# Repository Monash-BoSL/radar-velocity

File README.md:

# radar-velocity
Here we dedicate this repository to the development of a device to measure water surface velocity using mm wave radar

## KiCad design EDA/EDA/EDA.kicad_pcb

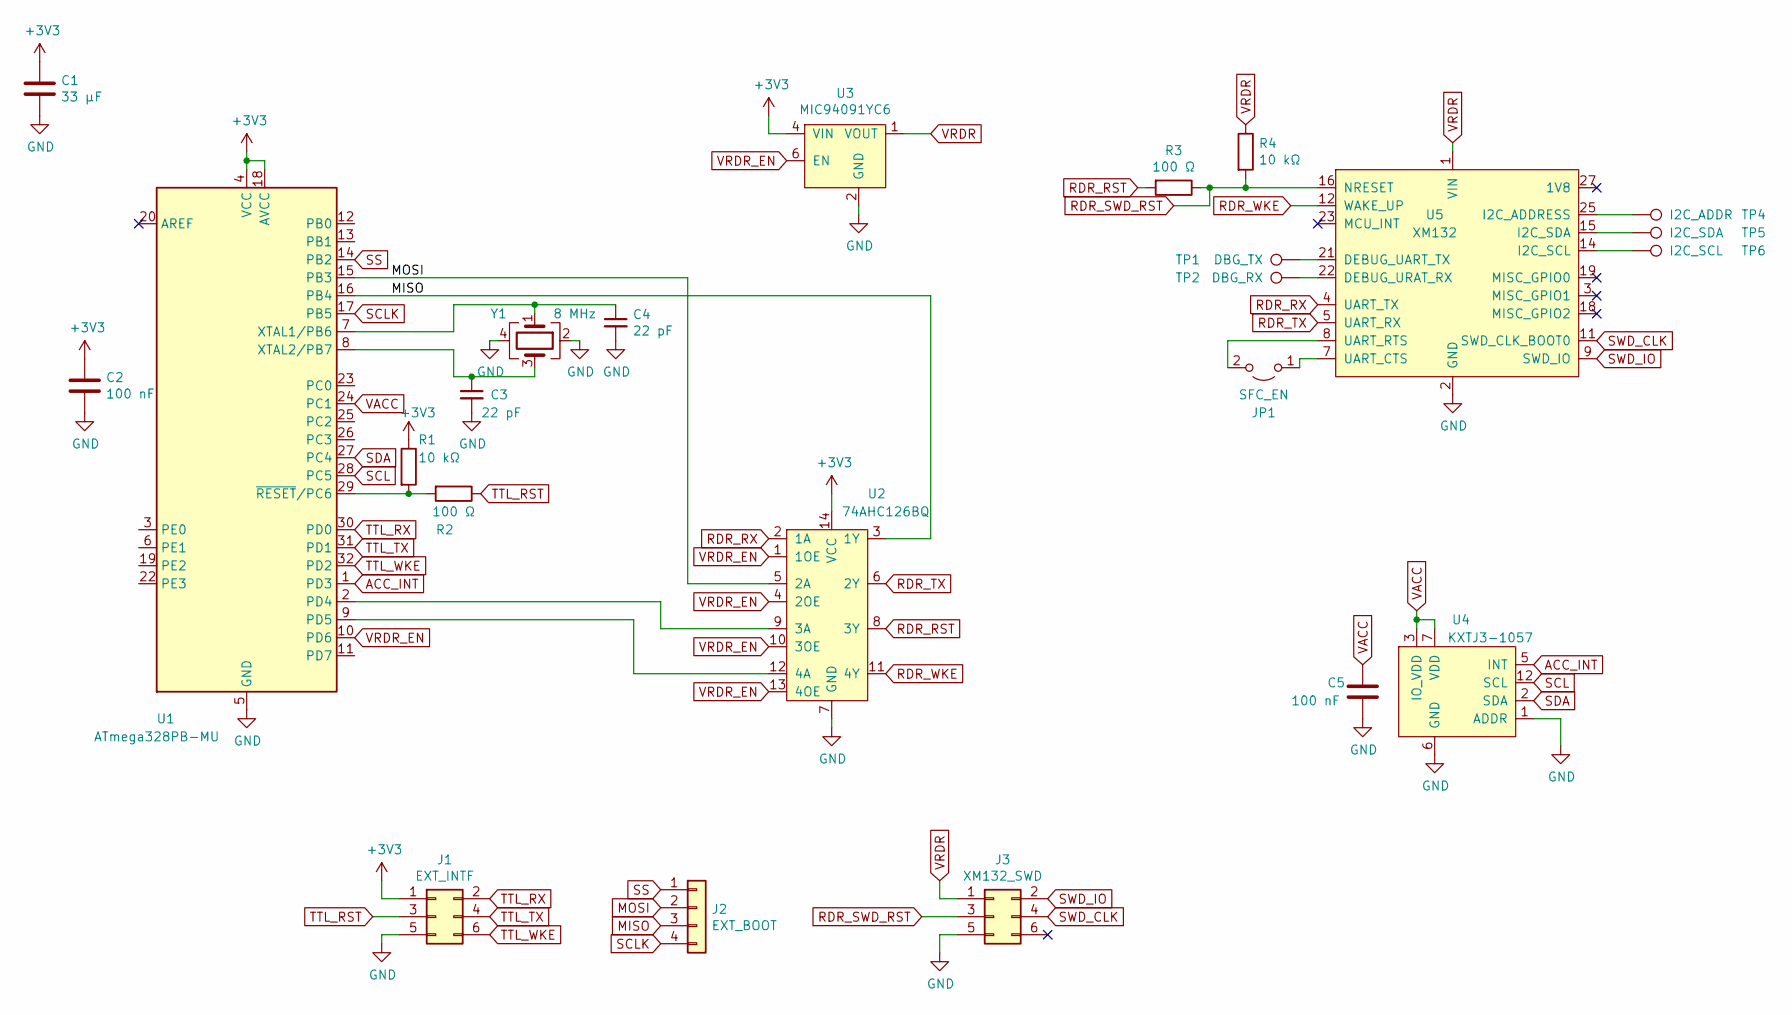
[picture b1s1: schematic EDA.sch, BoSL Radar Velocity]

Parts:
C1: 33 μF
C2, C5: 100 nF; C_0603_1608Metric
C3, C4: 22 pF; C_0603_1608Metric
J1: EXT_INTF; PinHeader_2x03_P1.27mm_Vertical
J2: EXT_BOOT; PinHeader_1x04_P1.27mm_Vertical
J3: XM132_SWD; PinHeader_2x03_P1.27mm_Vertical
JP1: SFC_EN; SolderJumper-2_P1.3mm_Open_Pad1.0x1.5mm
R1, R4: 10 kΩ; R_0603_1608Metric
R2, R3: 100 Ω; R_0603_1608Metric
TP1: DBG_TX; TestPoint_Pad_1.0x1.0mm
TP2: DBG_RX; TestPoint_Pad_1.0x1.0mm
TP4: I2C_ADDR; TestPoint_Pad_1.0x1.0mm
TP5: I2C_SDA; TestPoint_Pad_1.0x1.0mm
TP6: I2C_SCL; TestPoint_Pad_1.0x1.0mm
U1: ATmega328PB-MU; QFN-32-1EP_5x5mm_P0.5mm_EP3.1x3.1mm
U2: 74AHC126BQ; DHVQFN14
U3: MIC94091YC6; SOT-363_SC-70-6
U4: KXTJ3-1057; LGA-12_2x2mm_P0.5mm
U5: XM132
Y1: 8 MHz; Crystal_SMD_EuroQuartz_MT-4Pin_3.2x2.5mm

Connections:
+3V3: C1.1, C2.1, J1.1, R1.1, U1.4 (VCC), U1.18 (AVCC), U2.14 (VCC), U3.4 (VIN)
ACC_INT: U1.1 (PD3), U4.5 (INT)
GND: C1.2, C2.2, C3.2, C4.2, C5.2, J1.5, J3.5, U1.5 (GND), U1.21 (GND), U1.33 (GND), U2.7 (GND), U3.2 (GND), U3.5 (GND), U4.1 (ADDR), U4.6 (GND), U4.8 (GND), U4.9 (GND), U5.2 (GND), U5.6 (GND), U5.10 (GND), U5.13 (GND), U5.17 (GND), U5.20 (GND), U5.24 (GND), U5.26 (GND), U5.28 (GND), Y1.2, Y1.4
MISO: J2.3, U1.16 (PB4), U2.3 (1Y)
MOSI: J2.2, U1.15 (PB3), U2.5 (2A)
unnamed: C3.1, U1.8 (XTAL2/PB7), Y1.3
unnamed: C4.1, U1.7 (XTAL1/PB6), Y1.1
unnamed: JP1.1 (A), U5.7 (UART_CTS)
unnamed: JP1.2 (B), U5.8 (UART_RTS)
unnamed: R1.2, R2.2, U1.29 (~RESET~/PC6)
unnamed: TP1.1, U5.21 (DEBUG_UART_TX)
unnamed: TP2.1, U5.22 (DEBUG_URAT_RX)
unnamed: TP4.1, U5.25 (I2C_ADDRESS)
unnamed: TP5.1, U5.15 (I2C_SDA)
unnamed: TP6.1, U5.14 (I2C_SCL)
unnamed: U1.2 (PD4), U2.9 (3A)
unnamed: U1.9 (PD5), U2.12 (4A)
RDR_RST: R3.2, U2.8 (3Y)
RDR_RX: U2.2 (1A), U5.4 (UART_TX)
RDR_SWD_RST: J3.3, R3.1, R4.2, U5.16 (NRESET)
RDR_TX: U2.6 (2Y), U5.5 (UART_RX)
RDR_WKE: U2.11 (4Y), U5.12 (WAKE_UP)
SCL: U1.28 (PC5), U4.12 (SCL)
SCLK: J2.4, U1.17 (PB5)
SDA: U1.27 (PC4), U4.2 (SDA)
SS: J2.1, U1.14 (PB2)
SWD_CLK: J3.4, U5.11 (SWD_CLK_BOOT0)
SWD_IO: J3.2, U5.9 (SWD_IO)
TTL_RST: J1.3, R2.1
TTL_RX: J1.2, U1.30 (PD0)
TTL_TX: J1.4, U1.31 (PD1)
TTL_WKE: J1.6, U1.32 (PD2)
VACC: C5.1, U1.24 (PC1), U4.3 (IO_VDD), U4.7 (VDD), U4.10 (VDD), U4.11 (IO_VDD)
VRDR: J3.1, R4.1, U3.1 (VOUT), U5.1 (VIN)
VRDR_EN: U1.10 (PD6), U2.1 (1OE), U2.4 (2OE), U2.10 (3OE), U2.13 (4OE), U3.6 (EN)

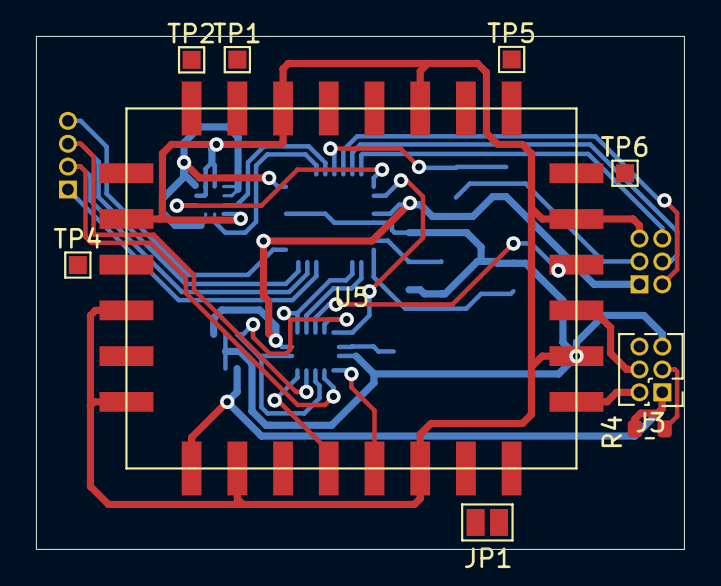
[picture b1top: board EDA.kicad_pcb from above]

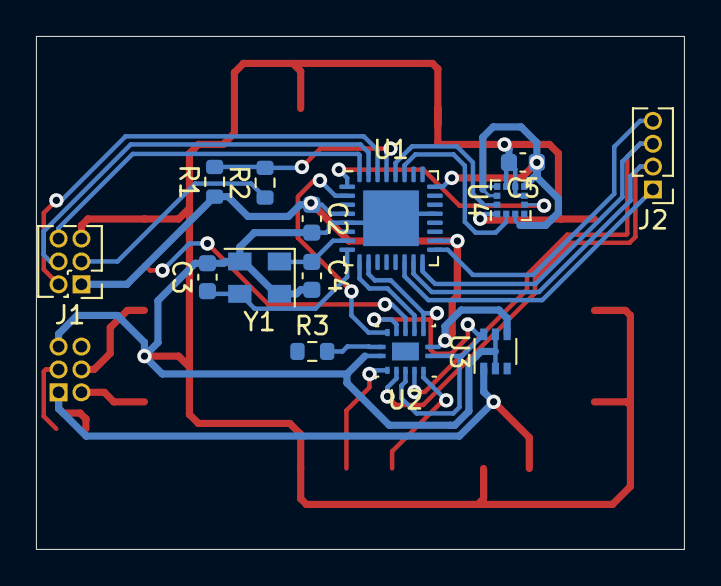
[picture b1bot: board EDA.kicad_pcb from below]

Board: 2 copper layers, 36.0 x 28.5 mm, 23 parts (14 on the bottom side), 35 nets.

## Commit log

2021-02-08 added initial verification data
2021-02-09 a design files for different lens options
2021-02-17 added python script to read sparse data from xm132
2021-02-17 added velocity readout to python acconeer tool
2021-02-28 finished (untested) cpp code for using XM132 module
2021-03-07 added accelorometer to schematic. completed most footprint association
2021-03-08 more work on PCB routing
